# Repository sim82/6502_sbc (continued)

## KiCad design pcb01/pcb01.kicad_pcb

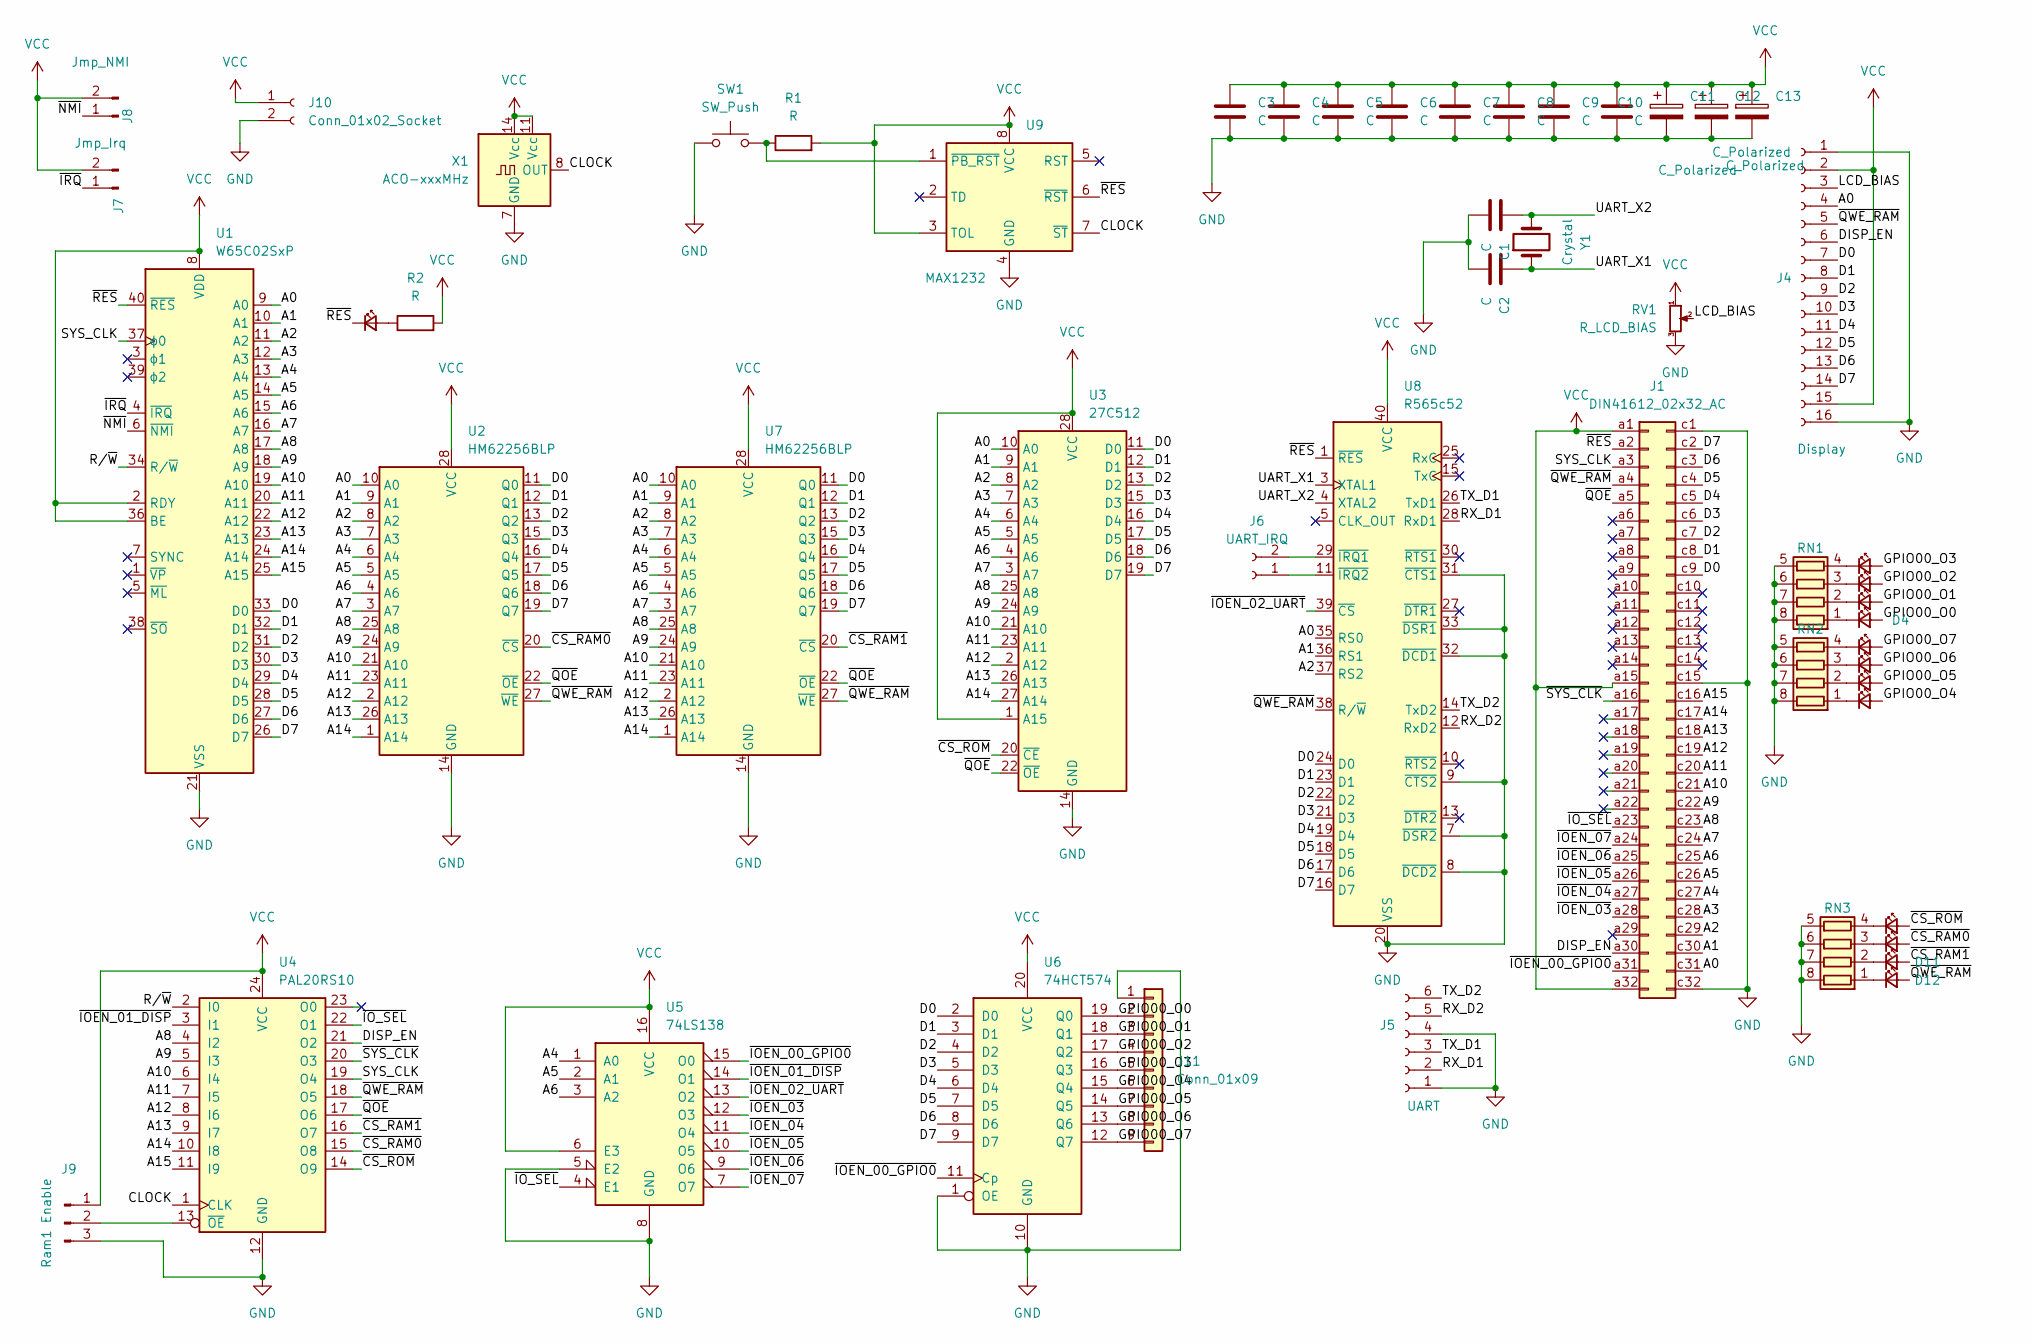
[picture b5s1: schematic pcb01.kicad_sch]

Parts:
C1, C2, C3, C4, C5, C6, C7, C8, C9, C10: C; C_Disc_D4.7mm_W2.5mm_P5.00mm
C11: C_Polarized; CP_Radial_D8.0mm_P5.00mm
C12, C13: C_Polarized; CP_Radial_D4.0mm_P2.00mm
D1, D2, D3, D4, D5, D6, D7, D8, D9, D10, D11, D12, D13: LED_Small; LED_0805_2012Metric_Pad1.15x1.40mm_HandSolder
J1: DIN41612_02x32_AC; DIN41612_C_2x32_Male_Horizontal_THT
J4: Display; PinSocket_1x16_P2.54mm_Vertical
J5: UART; PinSocket_1x06_P2.54mm_Vertical
J6: UART_IRQ; PinSocket_1x02_P2.54mm_Vertical
J7: Jmp_Irq; PinSocket_1x02_P2.54mm_Vertical
J8: Jmp_NMI; PinSocket_1x02_P2.54mm_Vertical
J9: Ram1 Enable; PinHeader_1x03_P2.54mm_Vertical
J10: Conn_01x02_Socket; PinSocket_1x02_P2.54mm_Vertical
J11: Conn_01x09; PinSocket_1x09_P2.54mm_Vertical
R1, R2: R; R_Axial_DIN0207_L6.3mm_D2.5mm_P7.62mm_Horizontal
RN1, RN2, RN3: R_Pack04; R_Array_Convex_4x0612
RV1: R_LCD_BIAS; Potentiometer_Vishay_T73YP_Vertical
SW1: SW_Push; SW_TH_Tactile_Omron_B3F-10xx
U1: W65C02SxP; DIP-40_W15.24mm_Socket
U2, U7: HM62256BLP; DIP-28_W7.62mm_Socket
U3: 27C512; DIP-28_W15.24mm_Socket
U4: PAL20RS10; DIP-24_W7.62mm_Socket
U5: 74LS138; DIP-16_W7.62mm_Socket
U6: 74HCT574; DIP-20_W7.62mm_Socket
U8: R565c52; DIP-40_W15.24mm_Socket
U9: MAX1232; SO-8_3.9x4.9mm_P1.27mm
X1: ACO-xxxMHz; DIP-14_W7.62mm
Y1: Crystal; Crystal_HC49-4H_Vertical

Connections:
/A0: J1.c31, J4.4, U1.9 (A0), U2.10 (A0), U3.10 (A0), U7.10 (A0), U8.35 (RS0)
/A1: J1.c30, U1.10 (A1), U2.9 (A1), U3.9 (A1), U7.9 (A1), U8.36 (RS1)
/A2: J1.c29, U1.11 (A2), U2.8 (A2), U3.8 (A2), U7.8 (A2), U8.37 (RS2)
/A3: J1.c28, U1.12 (A3), U2.7 (A3), U3.7 (A3), U7.7 (A3)
/A4: J1.c27, U1.13 (A4), U2.6 (A4), U3.6 (A4), U5.1 (A0), U7.6 (A4)
/A5: J1.c26, U1.14 (A5), U2.5 (A5), U3.5 (A5), U5.2 (A1), U7.5 (A5)
/A6: J1.c25, U1.15 (A6), U2.4 (A6), U3.4 (A6), U5.3 (A2), U7.4 (A6)
/A7: J1.c24, U1.16 (A7), U2.3 (A7), U3.3 (A7), U7.3 (A7)
/A8: J1.c23, U1.17 (A8), U2.25 (A8), U3.25 (A8), U4.4 (I2), U7.25 (A8)
/A9: J1.c22, U1.18 (A9), U2.24 (A9), U3.24 (A9), U4.5 (I3), U7.24 (A9)
/A10: J1.c21, U1.19 (A10), U2.21 (A10), U3.21 (A10), U4.6 (I4), U7.21 (A10)
/A11: J1.c20, U1.20 (A11), U2.23 (A11), U3.23 (A11), U4.7 (I5), U7.23 (A11)
/A12: J1.c19, U1.22 (A12), U2.2 (A12), U3.2 (A12), U4.8 (I6), U7.2 (A12)
/A13: J1.c18, U1.23 (A13), U2.26 (A13), U3.26 (A13), U4.9 (I7), U7.26 (A13)
/A14: J1.c17, U1.24 (A14), U2.1 (A14), U3.27 (A14), U4.10 (I8), U7.1 (A14)
/A15: J1.c16, U1.25 (A15), U4.11 (I9)
/CLOCK: U4.1 (CLK), U9.7 (~ST), X1.8 (OUT)
/D0: J1.c9, J4.7, U1.33 (D0), U2.11 (Q0), U3.11 (D0), U6.2 (D0), U7.11 (Q0), U8.24 (D0)
/D1: J1.c8, J4.8, U1.32 (D1), U2.12 (Q1), U3.12 (D1), U6.3 (D1), U7.12 (Q1), U8.23 (D1)
/D2: J1.c7, J4.9, U1.31 (D2), U2.13 (Q2), U3.13 (D2), U6.4 (D2), U7.13 (Q2), U8.22 (D2)
/D3: J1.c6, J4.10, U1.30 (D3), U2.15 (Q3), U3.15 (D3), U6.5 (D3), U7.15 (Q3), U8.21 (D3)
/D4: J1.c5, J4.11, U1.29 (D4), U2.16 (Q4), U3.16 (D4), U6.6 (D4), U7.16 (Q4), U8.19 (D4)
/D5: J1.c4, J4.12, U1.28 (D5), U2.17 (Q5), U3.17 (D5), U6.7 (D5), U7.17 (Q5), U8.18 (D5)
/D6: J1.c3, J4.13, U1.27 (D6), U2.18 (Q6), U3.18 (D6), U6.8 (D6), U7.18 (Q6), U8.17 (D6)
/D7: J1.c2, J4.14, U1.26 (D7), U2.19 (Q7), U3.19 (D7), U6.9 (D7), U7.19 (Q7), U8.16 (D7)
/DISP_EN: J1.a30, J4.6, U4.21 (O2)
/GPIO00_O0: D4.2 (A), J11.2, U6.19 (Q0)
/GPIO00_O1: D3.2 (A), J11.3, U6.18 (Q1)
/GPIO00_O2: D2.2 (A), J11.4, U6.17 (Q2)
/GPIO00_O3: D1.2 (A), J11.5, U6.16 (Q3)
/GPIO00_O4: D8.2 (A), J11.6, U6.15 (Q4)
/GPIO00_O5: D7.2 (A), J11.7, U6.14 (Q5)
/GPIO00_O6: D6.2 (A), J11.8, U6.13 (Q6)
/GPIO00_O7: D5.2 (A), J11.9, U6.12 (Q7)
/LCD_BIAS: J4.3, RV1.2
/RX_D1: J5.2, U8.28 (RxD1)
/RX_D2: J5.5, U8.12 (RxD2)
/R/~W: U1.34 (R/~W), U4.2 (I0)
/SYS_CLK: J1.a3, U1.37 (ϕ0), U4.19 (O4)
/TX_D1: J5.3, U8.26 (TxD1)
/TX_D2: J5.6, U8.14 (TxD2)
/UART_X1: C2.1, U8.3 (XTAL1), Y1.1
/UART_X2: C1.1, U8.4 (XTAL2), Y1.2
/~CS_RAM0: D10.2 (A), U2.20 (~CS), U4.15 (O8)
/~CS_RAM1: D11.2 (A), U4.16 (O7), U7.20 (~CS)
/~CS_ROM: D9.2 (A), U3.20 (~CE), U4.14 (O9)
/~IOEN_00_GPIO0: J1.a31, U5.15 (O0), U6.11 (Cp)
/~IOEN_01_DISP: U4.3 (I1), U5.14 (O1)
/~IOEN_02_UART: U5.13 (O2), U8.39 (~CS)
/~IOEN_03: J1.a28, U5.12 (O3)
/~IOEN_04: J1.a27, U5.11 (O4)
/~IOEN_05: J1.a26, U5.10 (O5)
/~IOEN_06: J1.a25, U5.9 (O6)
/~IOEN_07: J1.a24, U5.7 (O7)
/~IO_SEL: J1.a23, U4.22 (O1), U5.4 (E1)
/~IRQ: J7.1, U1.4 (~IRQ)
/~NMI: J8.1, U1.6 (~NMI)
/~QOE: J1.a5, U2.22 (~OE), U3.22 (~OE), U4.17 (O6), U7.22 (~OE)
/~QWE_RAM: D12.2 (A), J1.a4, J4.5, U2.27 (~WE), U4.18 (O5), U7.27 (~WE), U8.38 (R/~W)
/~RES: D13.1 (K), J1.a2, U1.40 (~RES), U8.1 (~RES), U9.6 (~RST)
/~SYS_CLK: J1.a16, U4.20 (O3)
GND: C1.2, C2.2, C3.2, C4.2, C5.2, C6.2, C7.2, C8.2, C9.2, C10.2, C11.2, C12.2, C13.2, J1.c1, J1.c15, J1.c32, J4.1, J4.16, J5.1, J5.4, J9.3, J10.2, J11.1, RN1.5 (R4.2), RN1.6 (R3.2), RN1.7 (R2.2), RN1.8 (R1.2), RN2.5 (R4.2), RN2.6 (R3.2), RN2.7 (R2.2), RN2.8 (R1.2), RN3.5 (R4.2), RN3.6 (R3.2), RN3.7 (R2.2), RN3.8 (R1.2), RV1.3, SW1.2, U1.21 (VSS), U2.14 (GND), U3.14 (GND), U4.12 (GND), U5.5 (E2), U5.8 (GND), U6.1 (OE), U6.10 (GND), U7.14 (GND), U8.7 (~DSR2), U8.8 (~DCD2), U8.9 (~CTS2), U8.20 (VSS), U8.31 (~CTS1), U8.32 (~DCD1), U8.33 (~DSR1), U9.4 (GND), X1.7 (GND)
unnamed: D1.1 (K), RN1.4 (R4.1)
unnamed: D2.1 (K), RN1.3 (R3.1)
unnamed: D3.1 (K), RN1.2 (R2.1)
unnamed: D4.1 (K), RN1.1 (R1.1)
unnamed: D5.1 (K), RN2.4 (R4.1)
unnamed: D6.1 (K), RN2.3 (R3.1)
unnamed: D7.1 (K), RN2.2 (R2.1)
unnamed: D8.1 (K), RN2.1 (R1.1)
unnamed: D9.1 (K), RN3.4 (R4.1)
unnamed: D10.1 (K), RN3.3 (R3.1)
unnamed: D11.1 (K), RN3.2 (R2.1)
unnamed: D12.1 (K), RN3.1 (R1.1)
unnamed: D13.2 (A), R2.1
unnamed: J6.1, U8.11 (~IRQ2)
unnamed: J6.2, U8.29 (~IRQ1)
unnamed: J9.2, U4.13 (~OE)
unnamed: R1.1, SW1.1, U9.1 (~PB_RST)
VCC: C3.1, C4.1, C5.1, C6.1, C7.1, C8.1, C9.1, C10.1, C11.1, C12.1, C13.1, J1.a1, J1.a15, J1.a32, J4.2, J4.15, J7.2, J8.2, J9.1, J10.1, R1.2, R2.2, RV1.1, U1.2 (RDY), U1.8 (VDD), U1.36 (BE), U2.28 (VCC), U3.1 (A15), U3.28 (VCC), U4.24 (VCC), U5.6 (E3), U5.16 (VCC), U6.20 (VCC), U7.28 (VCC), U8.40 (VCC), U9.3 (TOL), U9.8 (VCC), X1.11 (Vcc), X1.14 (Vcc)

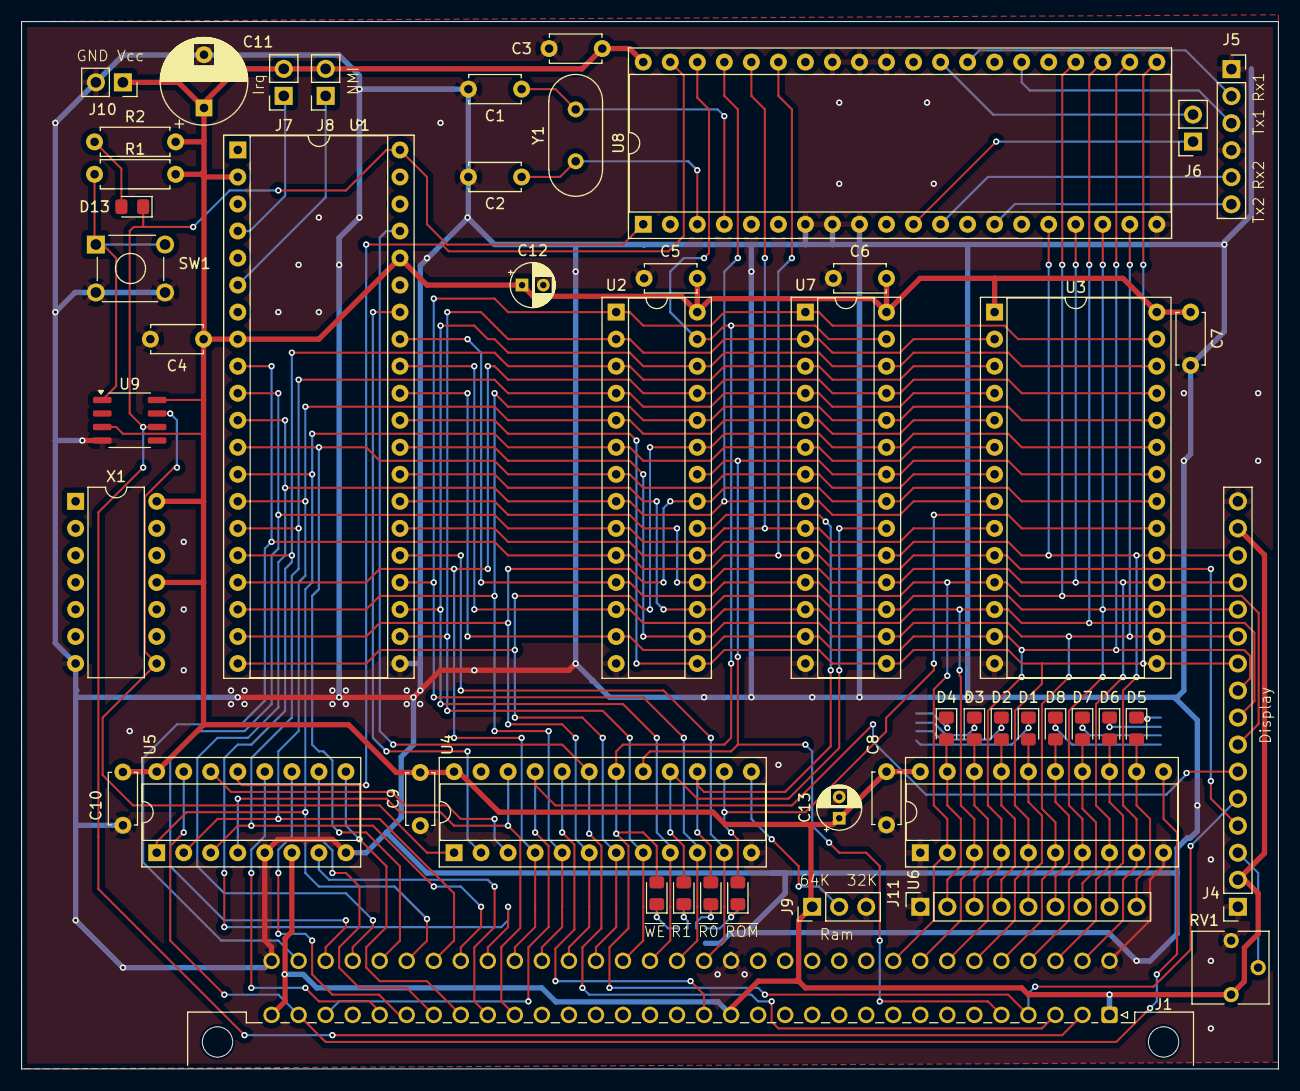
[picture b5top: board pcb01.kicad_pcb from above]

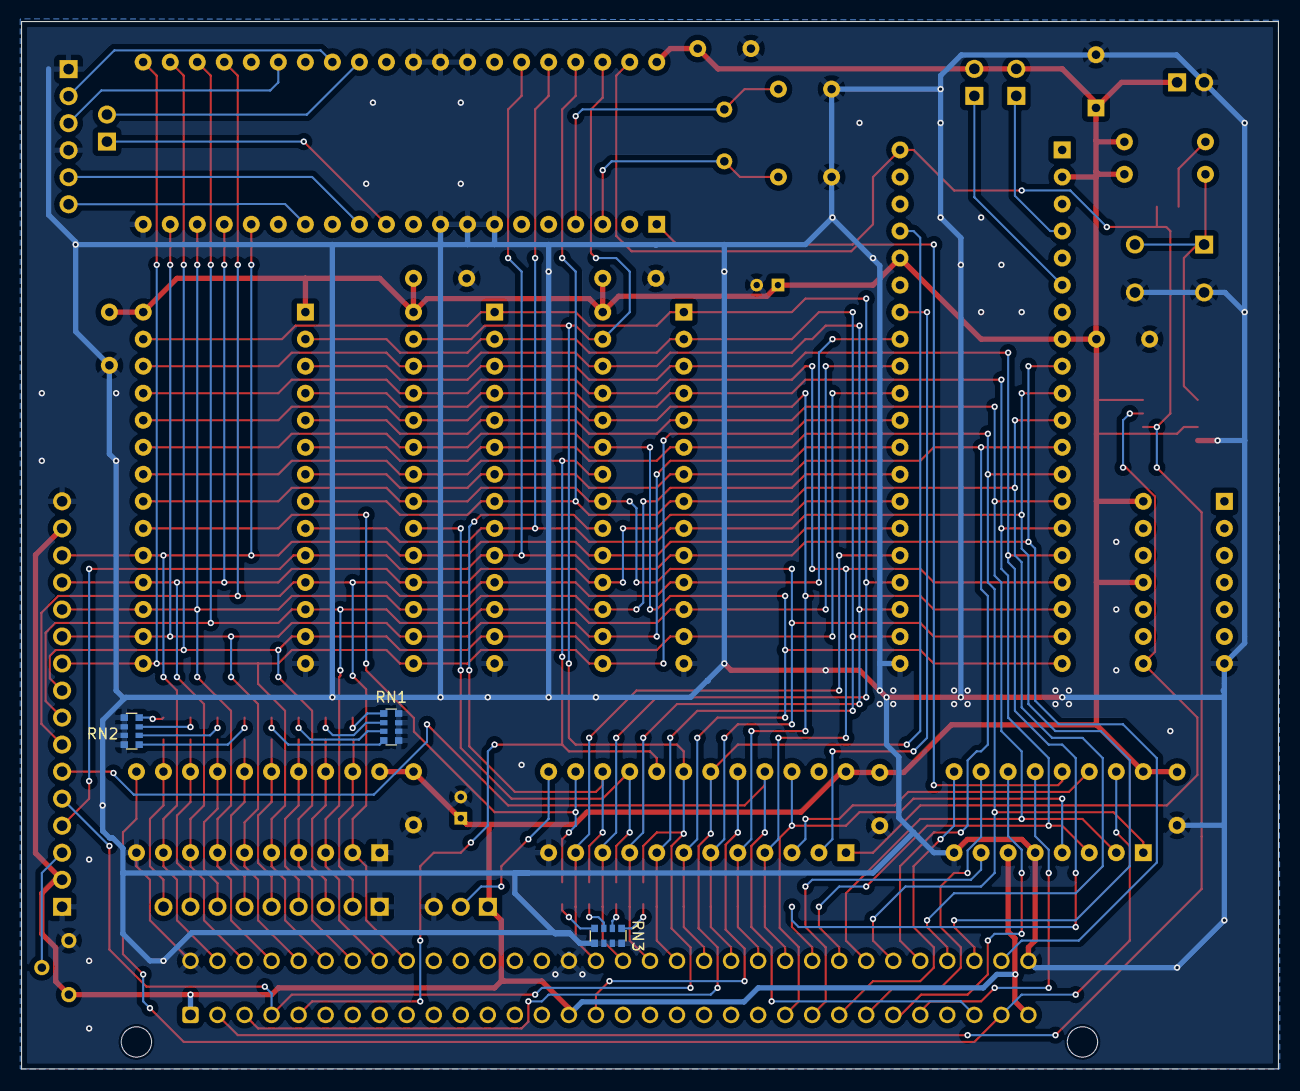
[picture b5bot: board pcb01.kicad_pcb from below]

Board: 2 copper layers, 118.1 x 98.4 mm, 53 parts (3 on the bottom side), 80 nets.
